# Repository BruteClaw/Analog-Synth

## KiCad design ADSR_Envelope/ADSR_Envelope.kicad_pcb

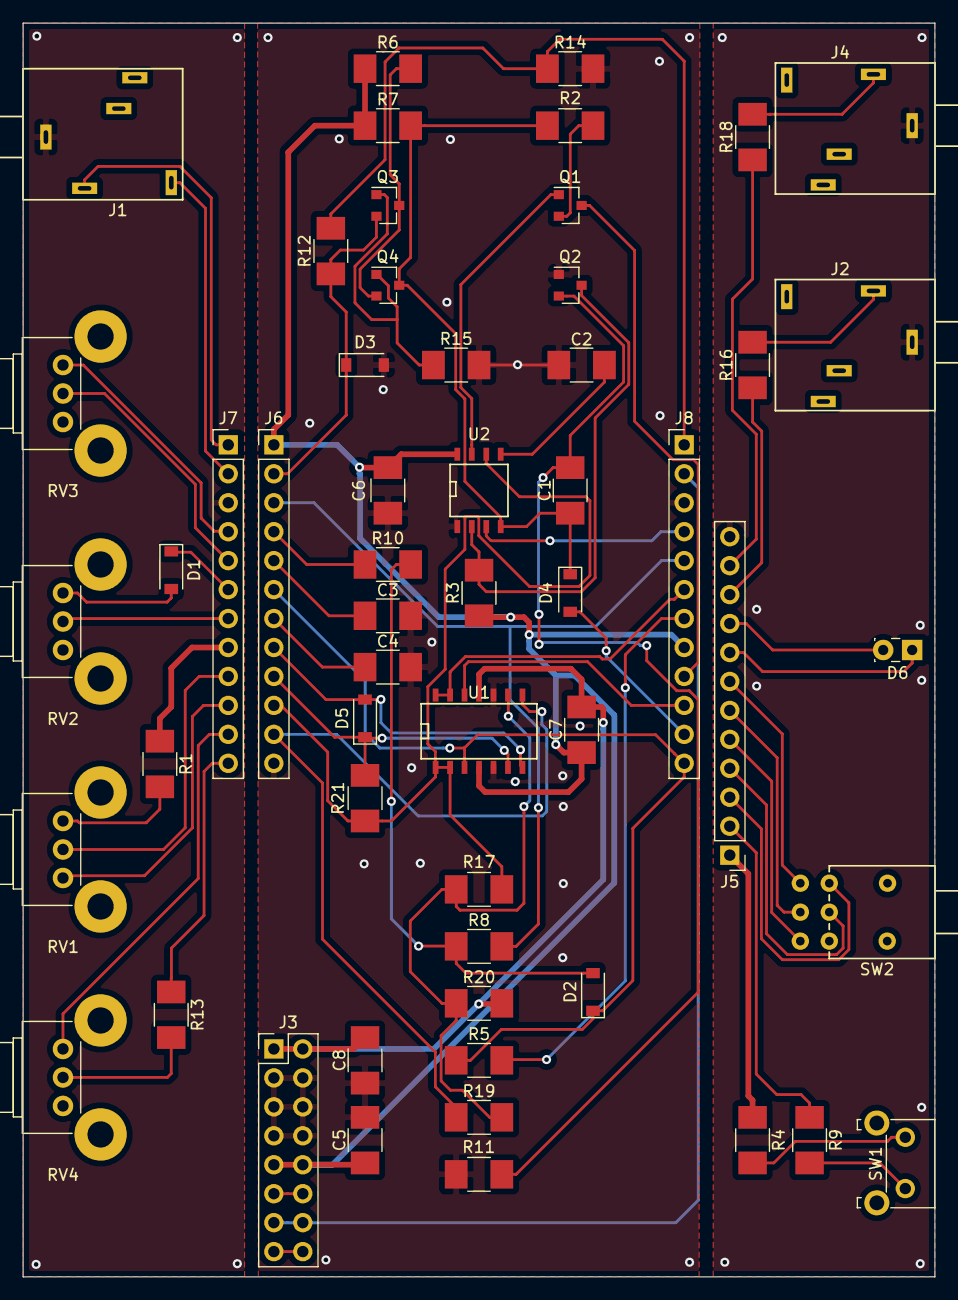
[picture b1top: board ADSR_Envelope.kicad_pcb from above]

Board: 2 copper layers, 80.0 x 110.0 mm, 55 parts (0 on the bottom side), 64 nets.

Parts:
C1, C2: 0.1u; C_1210_HandSoldering
C3: 1u; C_1210_HandSoldering
C4: 10u; C_1210_HandSoldering
C5, C8: 22u; C_1210_HandSoldering
C6, C7: 100u; C_1210_HandSoldering
D1, D2, D3, D4, D5: 1N4148; D_SOD-123
D6: LED; LED_Rectangular_W3.9mm_H1.9mm
J1, J2, J4: AudioJack1_Switch; Mono_Jack_3.5mm_Switch_Switchcraft_35RAPC2AH3
J3: Conn_02x08_Odd_Even; Pin_Header_Straight_2x08_Pitch2.54mm
J5, J6, J7, J8: Conn_01x12; Pin_Header_Straight_1x12_Pitch2.54mm
Q1: 2N7000; SOT-23
Q2, Q3, Q4: 2N3904; SOT-23
R1: 4.7k; R_1210_HandSoldering
R2, R12: 1M; R_1210_HandSoldering
R3, R6, R7, R11: 22k; R_1210_HandSoldering
R4: 10k; R_1210_HandSoldering
R5, R13: 100; R_1210_HandSoldering
R8: 680; R_1210_HandSoldering
R9: 47k; R_1210_HandSoldering
R10: 120; R_1210_HandSoldering
R14: 1.2M; R_1210_HandSoldering
R15: 10; R_1210_HandSoldering
R16, R18, R21: 1k; R_1210_HandSoldering
R17, R19: 100k; R_1210_HandSoldering
R20: 150k; R_1210_HandSoldering
RV1: 10k; Potentiometer_Bourns_PTV09A-2_Vertical
RV2, RV3, RV4: 500k; Potentiometer_Bourns_PTV09A-2_Vertical
SW1: SW_Push; SW_Tactile_TE_FSMRACDAH
SW2: SW_DPDT_x2; 200AWMDP1T2A1M6QE
U1: TL074; SOIC-14_N
U2: ICM7555; SOIC-8-N

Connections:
+12v: C5.1, C6.1, C7.1, J3.9, J3.10, J6.1, J8.8, R3.1, R6.1, R7.1, U1.4, U2.8
-12v: C7.2, C8.2, J3.1, J3.2, R20.2, U1.11
/12VDC_In: J7.8, R1.1
/12VDC_Out: J5.1, R4.1
/GND_In: J1.1, J7.3
/GND_Out: J2.1, J4.1, J5.12
ADSRInvert: J6.11, R19.1, U1.8
ADSRout: J6.10, R17.1, R21.2, U1.1, U1.2, U2.6
ATTin: J8.4, U2.3
ATTout: J6.3, J8.5, R8.2
Button: D3.1, J6.2, Q3.2, R12.1
DECin: J8.6, U1.13, U1.14
DECout: J8.7, R5.2
GND: C2.1, C3.2, C4.2, C5.2, C6.2, C8.1, D3.2, J3.3, J3.4, J3.5, J3.6, J3.7, J3.8, J6.12, J8.3, Q2.1, R11.2, R14.2, R15.2, U1.5, U1.10, U2.1
GateIn: J3.13, J3.14, J8.2
GateOut: J8.1, R12.2, R14.1
LEDin: D5.1, J6.9, R21.1, U1.6
LEDout: D5.2, J6.8, U1.7
unnamed: C1.1, D4.1, Q4.3, R2.2, R7.2, U2.4
unnamed: C1.2, Q2.2, R11.1
unnamed: C2.2, U2.5
unnamed: D1.1, J7.6
unnamed: D1.2, RV2.1
unnamed: D2.2, R8.1, R10.2
unnamed: D6.1, J5.8
unnamed: D6.2, J5.9
unnamed: J1.2, J7.2
unnamed: J1.3, J7.1
unnamed: J2.3, R16.2
unnamed: J3.11, J3.12
unnamed: J3.15, J3.16
unnamed: J4.3, R18.2
unnamed: J5.2, R9.1
unnamed: J5.3, SW2.1
unnamed: J5.4, SW2.2
unnamed: J5.5, SW2.6
unnamed: J5.6, SW2.5
unnamed: J5.7, SW2.4
unnamed: J5.10, R16.1
unnamed: J5.11, R18.1
unnamed: J7.4, RV3.1
unnamed: J7.5, RV3.2
unnamed: J7.7, RV2.2
unnamed: J7.9, RV1.2
unnamed: J7.10, RV1.3
unnamed: J7.11, RV4.1
unnamed: J7.12, R13.1
unnamed: Q1.1, U2.7
unnamed: Q1.2, R2.1
unnamed: Q2.3, R3.2, U2.2
unnamed: Q3.1, Q4.1, R15.1
unnamed: Q3.3, Q4.2, R6.2
unnamed: R1.2, RV1.1
unnamed: R4.2, SW1.1
unnamed: R9.2, SW1.2
unnamed: R13.2, RV4.2
unnamed: R17.2, R19.2, R20.1, U1.9
RELin: D4.2, J8.11
RELout: D2.1, J6.6, J8.12, R5.1, U1.3
SUSin: J8.9, Q1.3
SUSout: J8.10, U1.12
Speed1: J6.4, R10.1
Speed2: C4.1, J6.7
Speed3: C3.1, J6.5

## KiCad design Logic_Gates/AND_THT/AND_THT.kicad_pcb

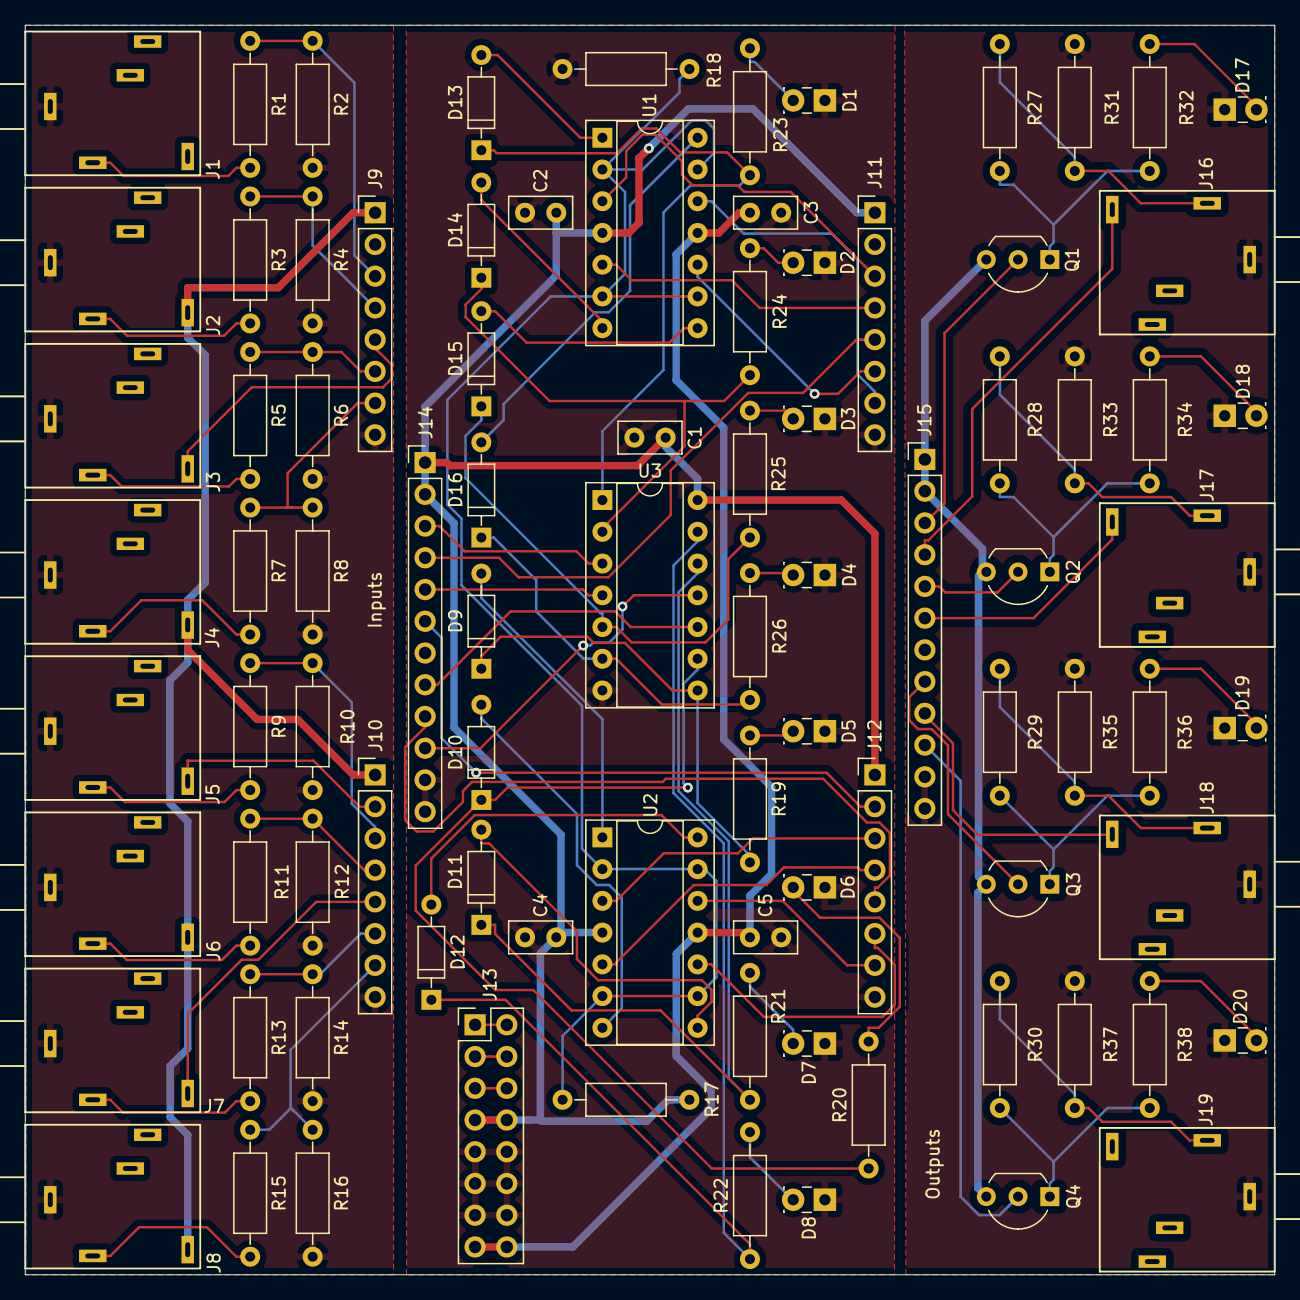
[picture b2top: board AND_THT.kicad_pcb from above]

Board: 2 copper layers, 100.0 x 100.0 mm, 89 parts (0 on the bottom side), 88 nets.

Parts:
C1, C2, C3, C4, C5: 10uF; C_Disc_D5.0mm_W2.5mm_P2.50mm
D1, D2, D3, D4, D5, D6, D7, D8, D17, D18, D19, D20: LED; LED_Rectangular_W3.9mm_H1.9mm
D9, D10, D11, D12, D13, D14, D15, D16: 1N4148; D_DO-35_SOD27_P7.62mm_Horizontal
J1, J2, J3, J4, J5, J6, J7, J8, J16, J17, J18, J19: AudioJack1_Switch; Mono_Jack_3.5mm_Switch_Switchcraft_35RAPC2AH3
J9, J10, J11, J12: Conn_01x08; Pin_Header_Straight_1x08_Pitch2.54mm
J13: Conn_02x08_Odd_Even; Pin_Header_Straight_2x08_Pitch2.54mm
J14, J15: Conn_01x12; Pin_Header_Straight_1x12_Pitch2.54mm
Q1, Q2, Q3, Q4: 2N3904; TO-92_Inline_Wide
R1, R3, R5, R7, R9, R11, R13, R15, R27, R28, R29, R30, R31, R33, R35, R37: 1k; R_Axial_DIN0207_L6.3mm_D2.5mm_P10.16mm_Horizontal
R2, R4, R6, R8, R10, R12, R14, R16, R17: 100k; R_Axial_DIN0207_L6.3mm_D2.5mm_P10.16mm_Horizontal
R18: 10k; R_Axial_DIN0207_L6.3mm_D2.5mm_P10.16mm_Horizontal
R19, R20, R21, R22, R23, R24, R25, R26, R32, R34, R36, R38: 2k7; R_Axial_DIN0207_L6.3mm_D2.5mm_P10.16mm_Horizontal
U1, U2: TL074; DIP-14_W7.62mm_Socket
U3: CD4081; DIP-14_W7.62mm_Socket

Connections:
+12VDC_A: J2.2, J4.2, J6.2, J8.2, J9.1, J10.1
+12V_B: C1.2, C2.2, C4.2, J11.1, J12.1, J13.7, J13.8, J14.1, J14.2, R17.2, U1.4, U2.4, U3.14
+12V_C: J15.1, J15.2, Q1.3, Q2.3, Q3.3, Q4.3
/1_Carry_A: J3.2, J9.5
/1_Carry_B: J11.5, J14.4
/1_Carry_C: J15.4, J16.2
/2_Carry_A: J5.2, J10.2
/2_Carry_B: J12.2, J14.6
/2_Carry_C: J15.6, J17.2
/3_Carry_A: J7.2, J10.5
/3_Carry_B: J12.5, J14.9
/3_Carry_C: J15.9, J18.2
/-12V_B: C3.1, C5.1, J13.15, J13.16, U1.11, U2.11
/GND_C: D17.1, D18.1, D19.1, D20.1, J15.11, J15.12, J16.1, J17.1, J18.1, J19.1, R31.1, R33.1, R35.1, R37.1
/IN1A_A: J9.3, R1.1, R2.1
/IN1A_B: J11.3, U1.3
/IN1B_A: J9.4, R3.1, R4.1
/IN1B_B: J11.4, U1.5
/IN2A_A: J9.6, R5.1, R6.1
/IN2A_B: J11.6, U1.10
/IN2B_A: J9.7, R7.1, R8.1
/IN2B_B: J11.7, U1.12
/IN3A_A: J10.3, R9.1, R10.1
/IN3A_B: J12.3, U2.3
/IN3B_A: J10.4, R11.1, R12.1
/IN3B_B: J12.4, U2.5
/IN4A_A: J10.6, R13.1, R14.1
/IN4A_B: J12.6, U2.10
/IN4B_A: J10.7, R15.1, R16.1
/IN4B_B: J12.7, U2.12
/Out1_B: J14.3, U3.3
/Out1_C: J15.3, Q1.2
/Out2_B: J14.5, U3.4
/Out2_C: J15.5, Q2.2
/Out3_B: J14.8, U3.10
/Out3_C: J15.8, Q3.2
/Out4_B: J14.10, U3.11
/Out4_C: J15.10, Q4.2
Bias: R17.1, R18.2, U1.2, U1.6, U1.9, U1.13, U2.2, U2.6, U2.9, U2.13
GND_A: J1.1, J2.1, J3.1, J4.1, J5.1, J6.1, J7.1, J8.1, J9.8, J10.8, R2.2, R4.2, R6.2, R8.2, R10.2, R12.2, R14.2, R16.2
GND_B: C1.1, C2.1, C3.2, C4.1, C5.2, D1.1, D2.1, D3.1, D4.1, D5.1, D6.1, D7.1, D8.1, J11.8, J12.8, J13.9, J13.10, J13.11, J13.12, J13.13, J13.14, J14.11, J14.12, R18.1, U3.7
unnamed: D1.2, R23.2
unnamed: D2.2, R24.2
unnamed: D3.2, R25.2
unnamed: D4.2, R26.2
unnamed: D5.2, R19.2
unnamed: D6.2, R20.2
unnamed: D7.2, R21.2
unnamed: D8.2, R22.2
unnamed: D9.1, R19.1, U3.8
unnamed: D9.2, U2.1
unnamed: D10.1, R20.1, U3.9
unnamed: D10.2, U2.7
unnamed: D11.1, R21.1, U3.12
unnamed: D11.2, U2.8
unnamed: D12.1, R22.1, U3.13
unnamed: D12.2, U2.14
unnamed: D13.1, R23.1, U3.1
unnamed: D13.2, U1.1
unnamed: D14.1, R24.1, U3.2
unnamed: D14.2, U1.7
unnamed: D15.1, R25.1, U3.5
unnamed: D15.2, U1.8
unnamed: D16.1, R26.1, U3.6
unnamed: D16.2, U1.14
unnamed: D17.2, R32.1
unnamed: D18.2, R34.1
unnamed: D19.2, R36.1
unnamed: D20.2, R38.1
unnamed: J1.3, R1.2
unnamed: J2.3, R3.2
unnamed: J3.3, R5.2
unnamed: J4.3, R7.2
unnamed: J5.3, R9.2
unnamed: J6.3, R11.2
unnamed: J7.3, R13.2
unnamed: J8.3, R15.2
unnamed: J13.1, J13.2
unnamed: J13.3, J13.4
unnamed: J13.5, J13.6
unnamed: J16.3, R27.1, R31.2
unnamed: J17.3, R28.1, R33.2
unnamed: J18.3, R29.1, R35.2
unnamed: J19.3, R30.1, R37.2
unnamed: Q1.1, R27.2, R32.2
unnamed: Q2.1, R28.2, R34.2
unnamed: Q3.1, R29.2, R36.2
unnamed: Q4.1, R30.2, R38.2

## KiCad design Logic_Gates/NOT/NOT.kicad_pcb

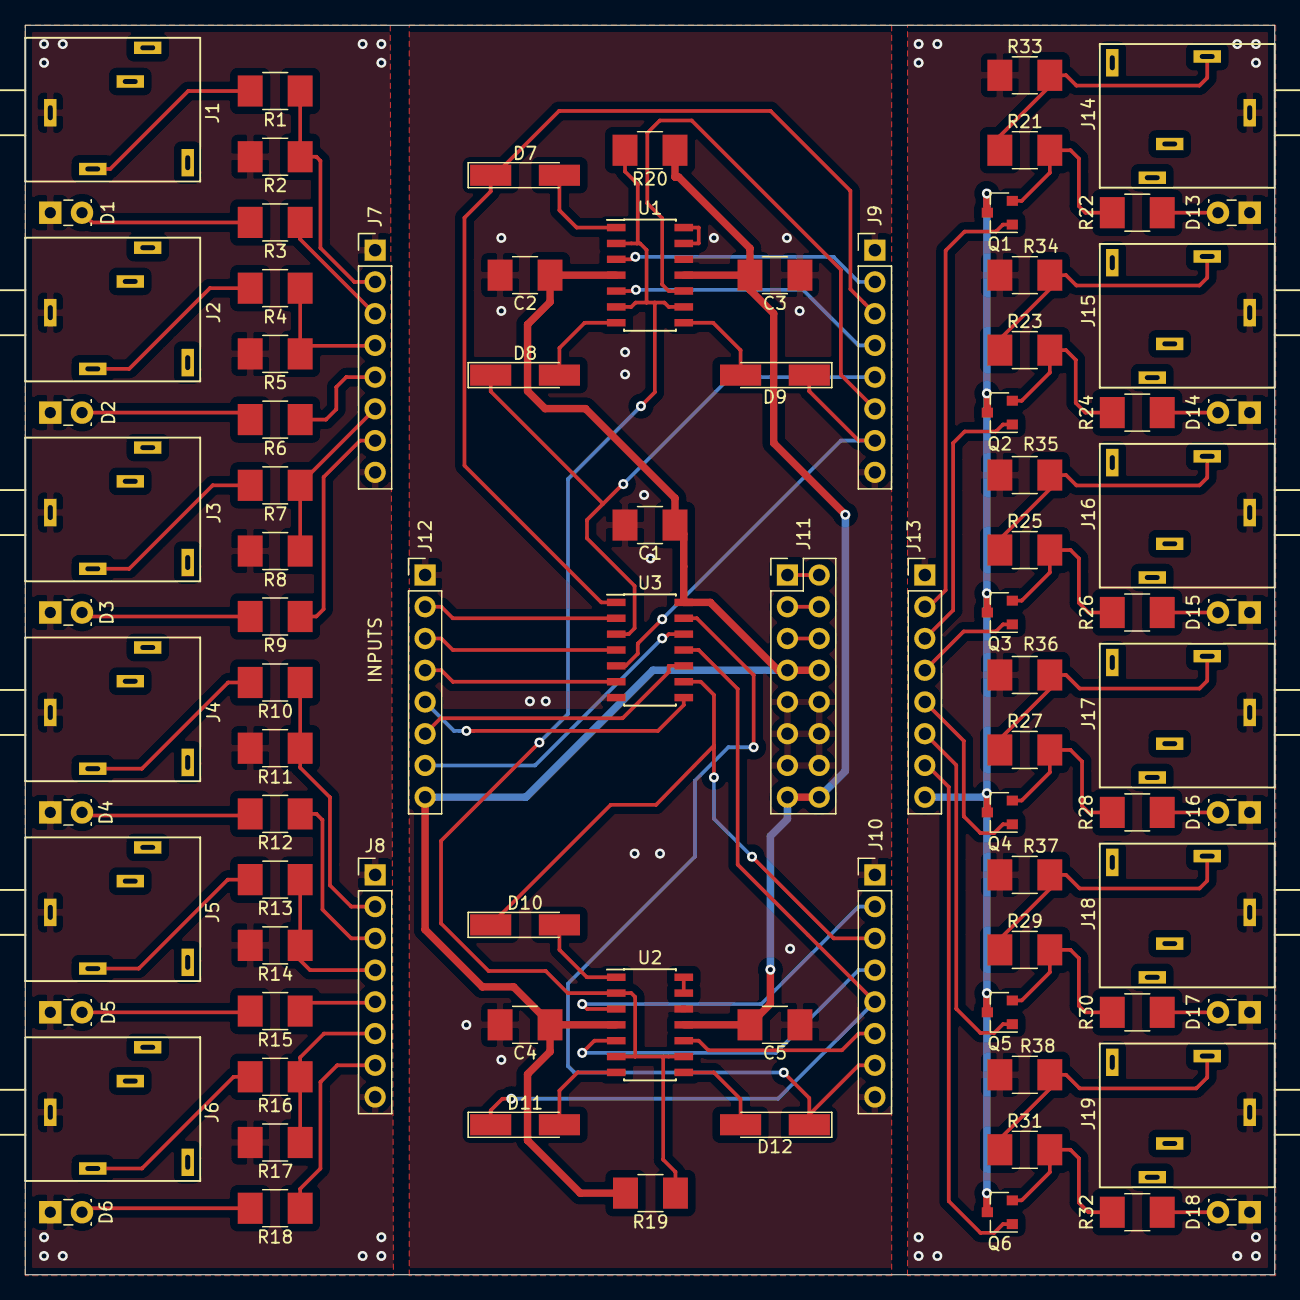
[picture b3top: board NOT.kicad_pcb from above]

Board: 2 copper layers, 100.0 x 100.0 mm, 89 parts (0 on the bottom side), 84 nets.

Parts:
C1, C2, C3, C4, C5: C; C_1210_HandSoldering
D1, D2, D3, D4, D5, D6, D13, D14, D15, D16, D17, D18: LED; LED_Rectangular_W3.9mm_H1.9mm
D7, D8, D9, D10, D11, D12: LL4148; D_MiniMELF_Handsoldering
J1, J2, J3, J4, J5, J6, J14, J15, J16, J17, J18, J19: AudioJack1_Switch; Mono_Jack_3.5mm_Switch_Switchcraft_35RAPC2AH3
J7, J8, J9, J10, J12, J13: Conn_01x08; Pin_Header_Straight_1x08_Pitch2.54mm
J11: Conn_02x08_Odd_Even; Pin_Header_Straight_2x08_Pitch2.54mm
Q1, Q2, Q3, Q4, Q5, Q6: MMBT3904; SOT-23
R1, R4, R7, R10, R13, R16, R21, R23, R25, R27, R29, R31, R33, R34, R35, R36, R37, R38: 1K; R_1210_HandSoldering
R2, R5, R8, R11, R14, R17, R19: 100K; R_1210_HandSoldering
R3, R6, R9, R12, R15, R18, R22, R24, R26, R28, R30, R32: 2k7; R_1210_HandSoldering
R20: 10K; R_1210_HandSoldering
U1, U2: TL074; SOIC-14_3.9x8.7mm_Pitch1.27mm
U3: CD4069; SOIC-14_3.9x8.7mm_Pitch1.27mm

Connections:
+12VDC_B: C1.1, C2.1, C4.1, J11.7, J11.8, J12.8, R19.2, U1.4, U2.4, U3.14
+12VDC_C: J13.8, Q1.3, Q2.3, Q3.3, Q4.3, Q5.3, Q6.3
-12VDC: C3.2, C5.2, J11.15, J11.16, R20.1, U1.11, U2.11
/In1: J7.2, R1.1, R2.1
/In1_LED: J7.3, R3.1
/In2: J7.4, R4.1, R5.1
/In2_LED: J7.5, R6.1
/In3: J7.6, R7.1, R8.1
/In3_LED: J7.7, R9.1
/In4: J8.2, R10.1, R11.1
/In4_LED: J8.3, R12.1
/In5: J8.4, R13.1, R14.1
/In5_LED: J8.5, R15.1
/In6: J8.6, R16.1, R17.1
/In6_LED: J8.7, R18.1
/Out1: J13.2, Q1.1
/Out2: J13.3, Q2.1
/Out3: J13.4, Q3.1
/Out4: J13.5, Q4.1
/Out5: J13.6, Q5.1
/Out6: J13.7, Q6.1
Bias: R19.1, R20.2, U1.2, U1.6, U1.9, U2.2, U2.6, U2.9
GND_A: D1.1, D2.1, D3.1, D4.1, D5.1, D6.1, J1.1, J2.1, J3.1, J4.1, J5.1, J6.1, J7.1, J7.8, J8.1, J8.8, R2.2, R5.2, R8.2, R11.2, R14.2, R17.2
GND_B: C1.2, C2.2, C3.1, C4.2, C5.1, J9.1, J9.8, J10.1, J10.8, J11.9, J11.10, J11.11, J11.12, J11.13, J11.14, J12.1, U1.12, U2.12, U3.7
GND_C: D13.1, D14.1, D15.1, D16.1, D17.1, D18.1, J13.1, J14.1, J15.1, J16.1, J17.1, J18.1, J19.1, R33.1, R34.1, R35.1, R36.1, R37.1, R38.1
unnamed: D1.2, R3.2
unnamed: D2.2, R6.2
unnamed: D3.2, R9.2
unnamed: D4.2, R12.2
unnamed: D5.2, R15.2
unnamed: D6.2, R18.2
unnamed: D7.1, J9.3, U3.1
unnamed: D7.2, U1.1
unnamed: D8.1, J9.5, U3.3
unnamed: D8.2, U1.7
unnamed: D9.1, J9.7, U3.5
unnamed: D9.2, U1.8
unnamed: D10.1, J10.3, U3.9
unnamed: D10.2, U2.1
unnamed: D11.1, J10.5, U3.11
unnamed: D11.2, U2.7
unnamed: D12.1, J10.7, U3.13
unnamed: D12.2, U2.8
unnamed: D13.2, R22.1
unnamed: D14.2, R24.1
unnamed: D15.2, R26.1
unnamed: D16.2, R28.1
unnamed: D17.2, R30.1
unnamed: D18.2, R32.1
unnamed: J1.3, R1.2
unnamed: J2.3, R4.2
unnamed: J3.3, R7.2
unnamed: J4.3, R10.2
unnamed: J5.3, R13.2
unnamed: J6.3, R16.2
unnamed: J9.2, U1.3
unnamed: J9.4, U1.5
unnamed: J9.6, U1.10
unnamed: J10.2, U2.3
unnamed: J10.4, U2.5
unnamed: J10.6, U2.10
unnamed: J11.1, J11.2
unnamed: J11.3, J11.4
unnamed: J11.5, J11.6
unnamed: J12.2, U3.2
unnamed: J12.3, U3.4
unnamed: J12.4, U3.6
unnamed: J12.5, U3.8
unnamed: J12.6, U3.10
unnamed: J12.7, U3.12
unnamed: J14.3, R21.1, R33.2
unnamed: J15.3, R23.1, R34.2
unnamed: J16.3, R25.1, R35.2
unnamed: J17.3, R27.1, R36.2
unnamed: J18.3, R29.1, R37.2
unnamed: J19.3, R31.1, R38.2
unnamed: Q1.2, R21.2, R22.2
unnamed: Q2.2, R23.2, R24.2
unnamed: Q3.2, R25.2, R26.2
unnamed: Q4.2, R27.2, R28.2
unnamed: Q5.2, R29.2, R30.2
unnamed: Q6.2, R31.2, R32.2
unnamed: U1.13, U1.14
unnamed: U2.13, U2.14
